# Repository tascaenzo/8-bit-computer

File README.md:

# CPU 8-bit

Repository di supporto alla serie didattica YouTube in cui viene progettata e costruita una CPU a 8 bit partendo dai blocchi logici fondamentali.

In questa fase il repository contiene documentazione, una prima ISA, esempi assembly, un assembler in C e strumenti di supporto per programmare le memorie della CPU.

## Contenuto

```text
.
├── docs/
├── examples/
│   └── assembly/
├── hardware/
│   └── tang-nano-9k-video/
├── tools/
│   ├── assembler/
│   ├── cu-bytecode/
│   └── eeprom-programmer/
├── wiki/
│   ├── blog/
│   └── videos/
└── README.md
```

### `docs`

Contiene la documentazione tecnica della CPU:

- [`docs/isa.md`](docs/isa.md) definisce architettura, istruzioni e opcode;
- [`docs/assembly-language.md`](docs/assembly-language.md) definisce la sintassi dei programmi assembly.
- [`docs/control-unit-microcode.md`](docs/control-unit-microcode.md) definisce segnali e microsequenze della Control Unit.
- [`docs/video-hdmi.md`](docs/video-hdmi.md) definisce VRAM e uscita HDMI della Tang Nano 9K.
- [`docs/io-ps2-timer.md`](docs/io-ps2-timer.md) definisce registri I/O, tastiera PS/2 e timer della Tang Nano 9K.

### `examples/assembly`

Contiene programmi assembly didattici usati per provare l'assembler e spiegare le istruzioni della CPU.

### `hardware/tang-nano-9k-video`

Contiene il progetto FPGA video completo: interfaccia CPU, VRAM 16 KiB,
font ASCII e uscita HDMI 640 × 480. Il [README FPGA](hardware/tang-nano-9k-video/README.md)
include build, test, pinout e caricamento del bitstream. La build e' verificata
con OSS CAD Suite; il collaudo sulla scheda fisica resta da eseguire.

### `tools/assembler`

Contiene `cpu8asm`, l'assembler in C che traduce i programmi assembly in byte macchina.

### `tools/eeprom-programmer`

Contiene sketch e documentazione per programmare EEPROM parallele usate dalla CPU, come la AT28C64.

La guida passo passo per il programmatore AT28C64 con Arduino Mega e in:

```text
docs/at28c64-arduino-mega-programmer.md
```

### `tools/cu-bytecode`

Contiene `cpu8microcode`, il generatore C delle tre Control ROM e della ROM di
dispatch. La guida di build e la mappa dei bit sono in
[`tools/cu-bytecode/README.md`](tools/cu-bytecode/README.md).

### `tools/simulator-web`

Contiene il simulatore web step-by-step della ISA: permette di assemblare ed
eseguire programmi nel browser, osservando registri, flag, RAM e la memoria
video mappata nella FPGA. La guida di avvio è in
[`tools/simulator-web/README.md`](tools/simulator-web/README.md).

### `wiki/videos`

Contiene le trascrizioni autogenerate dei video della serie.

Le trascrizioni sono materiale grezzo: possono contenere errori di riconoscimento, frasi incomplete o termini tecnici interpretati male. Servono come base di lavoro per ricostruire gli argomenti trattati nei video.

### `wiki/blog`

Contiene articoli tecnici in italiano ricavati dalle trascrizioni e dagli argomenti gia affrontati.

Gli articoli seguono il percorso reale della serie e non anticipano parti non ancora consolidate.

## Argomenti documentati

Finora la documentazione copre:

- operazioni logiche della ALU: `AND`, `OR`, `XOR`, `NOR`, `NAND`, `XNOR`, `NOT`;
- pull-up, pull-down e comportamento dei livelli logici;
- buffer tri-state e collegamento al bus dati;
- somma binaria con half adder e full adder;
- complemento a due e numeri con segno;
- somma e sottrazione con il 74283;
- flag `Carry`, `Negative`, `Zero` e `Overflow`;
- operazioni di confronto tramite flag;
- codice operazione della ALU;
- segnale di clock;
- flip-flop `SR` e `D`.

## Convenzioni

- La documentazione principale e in italiano.
- I nomi tecnici possono restare in inglese quando corrispondono meglio a datasheet, segnali o architettura.
- Le trascrizioni autogenerate non sono considerate documentazione definitiva: vanno ripulite e corrette quando vengono trasformate in articoli.

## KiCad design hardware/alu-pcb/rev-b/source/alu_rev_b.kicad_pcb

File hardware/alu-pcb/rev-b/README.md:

# CPU8 — PCB ALU rev. B

Pacchetto per fabbricare una **scheda nuda da saldare**, con sorgenti KiCad.
Versione del 7 ottobre 2026: ALU combinatoria a 8 bit, logica **74HCT a 5 V**,
registri RA/RB e registro dei flag **esterni**. La revisione B aggiunge indicatori e comandi locali alla revisione A.

## File da usare

- `CPU8_ALU_REV_B_GERBER.zip`: caricare questo ZIP nel preventivatore PCB.
- `CPU8_ALU_REV_B_PROJECT.zip`: progetto modificabile e documentazione.
- `source/alu_rev_b.kicad_pro`: aprire in KiCad per accedere a schema e PCB.
- `alu_rev_b_schematic.pdf`: schema completo, con tutti i pin e le reti.
- `BOM.csv`: componenti da acquistare per il montaggio manuale.
- `alu_rev_b_preview.png`: anteprima della scheda nuda.
- `alu_rev_b_layout.svg`: visualizzazione delle piste e della serigrafia.

Lo ZIP Gerber non include i componenti: non è un ordine di assemblaggio.
Non sono stati effettuati ordini o caricamenti sui siti dei produttori.

## Parametri per l'ordine

| Parametro | Impostazione |
| --- | --- |
| Dimensioni | 290 × 300 mm |
| Materiale | FR-4 |
| Strati rame | 2 |
| Spessore | 1,6 mm |
| Rame | 1 oz |
| Maschera | Verde, entrambi i lati |
| Serigrafia | Bianca, fronte |
| Finitura | HASL senza piombo oppure ENIG |
| Assemblaggio | Nessuno; componenti saldati a mano |
| Stencil | Nessuno |
| Via | Diametro rame 0,70 mm, foro 0,30 mm |
| Fori componenti | 0,80 e 0,90 mm, metallizzati |
| Fori montaggio | Quattro fori da 3,20 mm, non metallizzati |

Le piste sono generalmente da 0,30 mm, con restringimenti locali fino a
0,15 mm. Le regole di clearance del progetto sono 0,25 mm; clearance minima
assoluta verificata 0,20 mm. Gli anelli delle via sono da 0,20 mm.
Le capacità pubblicate da [JLCPCB](https://jlcpcb.com/capabilities/Capabilities)
e [PCBWay](https://www.pcbway.com/capabilities.html) consentono queste dimensioni
con rame da 1 oz. Verificare che l'anteprima del produttore riconosca tutti
i layer e i due file di foratura e mostri 290 × 300 mm.

## Cosa contiene la scheda

Dieci operazioni, due sommatori a quattro bit in cascata, selezione del
risultato mediante otto multiplexer, buffer tri-state del bus e flag
combinatori C/Z/N/O. Nessun clock è necessario sulla scheda: i registri che
catturano dati e flag si trovano all'esterno.

La selezione mediante multiplexer modifica l'implementazione fisica descritta
negli articoli con decoder e buffer separati, mantenendo la semantica della ISA.
Non si tratta di una copia delle connessioni della millefori esistente.

| OP3 OP2 OP1 OP0 | Operazione | Risultato |
| --- | --- | --- |
| 0000 | AND | A AND B |
| 0001 | OR | A OR B |
| 0010 | XOR | A XOR B |
| 0011 | NOR | NOT(A OR B) |
| 0100 | NAND | NOT(A AND B) |
| 0101 | XNOR | NOT(A XOR B) |
| 0110 | NOT | NOT A |
| 0111 | ADD | A + B, modulo 256 |
| 1000 | SUB | A - B, modulo 256 |
| 1001 | CMP | Sottrazione interna; bus disabilitato |
| 1010–1111 | Riservate | Bus disabilitato; flag non definiti per la ISA |

C indica carry in ADD e **borrow** in SUB/CMP. Z indica risultato zero;
N è il bit 7 del risultato; O indica overflow signed. C e O sono azzerati
per le operazioni logiche. I flag derivano dal risultato interno, anche quando
il buffer del bus è disabilitato.

## LED e modalità autonoma

- **16 LED verdi** mostrano A7…A0 e B7…B0 dopo la selezione della sorgente.
- **4 LED gialli** mostrano C, Z, N e O del risultato interno.
- **10 LED blu** mostrano AND, OR, XOR, NOR, NAND, XNOR, NOT, ADD, SUB e CMP.
  Gli opcode riservati non accendono alcun LED di operazione.
- **SW4 OFF = esterna**, **SW4 ON = locale**. Sei 74HCT157 commutano tutti
  i 21 segnali: A, B, opcode e ALU_EN_n. Le due sorgenti restano separate;
  gli interruttori non portano +5 V sulle uscite dei moduli esterni.
- **SW1** imposta A, **SW2** B: da sinistra bit 7, 6, 5, 4, 3, 2, 1, 0.
  **SW3** imposta l'opcode: da sinistra OP3, OP2, OP1, OP0.
  Per ciascun contatto, OFF = 0 e ON = 1.
- **SW5 OFF** disabilita il bus in modalità locale; **SW5 ON** lo abilita.
  CMP e gli opcode riservati mantengono comunque J4 in alta impedenza.
  In modalità esterna SW5 non interviene: decide J3 pin 5.

Per il primo test standalone collegare solo J6 a 5 V regolati e GND,
lasciare J4 scollegato, mettere SW4 ON e scegliere A/B/OP mediante SW1–SW3.
Il risultato interno è disponibile su J7; i LED indicano operandi, flag e
operazione. Questa revisione non include otto LED di risultato.
Esempio ADD: SW1 = 11111111, SW2 = 00000001, SW3 = 0111:
si accendono ADD, C e Z; N/O sono spenti; J7 vale 00.

I LED di A/B/flag sono pilotati da tre buffer 74HCT244 dedicati;
i due 74HCT138 decodificano l'operazione. Ogni LED ha una resistenza da
2,2 kΩ, con corrente nell'ordine di 1 mA: usare LED ad alta efficienza.
I flag sono combinatori e non memorizzati: possono cambiare durante lo
spostamento dei DIP switch. Cambiare sorgente con il bus disabilitato
su entrambe le sorgenti e attendere l'assestamento prima della cattura.

## Connettori

Tutti i connettori hanno due colonne, passo 2,54 mm. Guardando il lato componenti,
con il testo della scheda in alto, il pin 1 è la piazzola quadrata in alto a
sinistra. La prima riga contiene 1/2, la seconda 3/4, e così via.
La piedinatura è specifica di questa scheda: preparare i cavi di conseguenza.

| Connettore | Pin | Segnali |
| --- | --- | --- |
| J1 A_INPUT | 1–8; 9–10 | A0…A7; GND, GND |
| J2 B_INPUT | 1–8; 9–10 | B0…B7; GND, GND |
| J3 CONTROL | 1, 2, 3, 4 | OP0, OP1, OP2, OP3 |
| J3 CONTROL | 5; 6–8 | ALU_EN_n; GND, GND, GND |
| J4 DATA_BUS | 1–8; 9–10 | D0…D7; GND, GND |
| J5 FLAGS_CZNO | 1–6 | C, Z, N, O, GND, GND |
| J6 POWER_5V | 1–4 | +5V, GND, +5V, GND |
| J7 RESULT_TEST | 1–8; 9–10 | R0…R7 interni; GND, GND |

ALU_EN_n = 1 disabilita l'uscita sul bus. ALU_EN_n = 0 la abilita solo
per OP 0…8; CMP e gli opcode riservati lasciano comunque D in alta impedenza.
Un pull-up da 4,7 kΩ disabilita l'uscita quando il controllo è scollegato.
A/B/opcode hanno pull-down da 10 kΩ.

J5 e J7 sono uscite push-pull: usarle come ingressi di altri circuiti o punti
di misura, senza collegarle a un bus pilotato da altre sorgenti. J4 è l'unica
uscita dati tri-state. Collegare le masse dei moduli.

Gli ingressi HCT accettano livelli TTL, ma alimentare questa scheda con 5 V
regolati; non collegare le sue uscite da 5 V direttamente a una FPGA a 3,3 V.
La compatibilità e il carico dei moduli esterni vanno verificati con le sigle
complete degli integrati effettivamente utilizzati.

## Componenti e montaggio

La distinta contiene 172 componenti: 45 IC, 45 condensatori da 100 nF, un
condensatore da 10 µF, sei reti resistive, 33 resistori, sette connettori,
30 LED e cinque DIP switch. Aggiungere **23 zoccoli DIP-14, 18 DIP-16 e quattro DIP-20**, tutti larghi 7,62 mm.
Non sostituire i package DIP con SOIC. Per i multiplexer utilizzare CD74HCT151E:
la distinzione fra uscita diretta Y (pin 5) e complementare W (pin 6) segue
il datasheet TI attuale.

- Orientare la tacca degli IC verso l'alto; il pin 1 ha piazzola quadrata.
- RN1…RN6 devono essere **reti bussed SIP-9**, comune al pin 1:
  otto resistenze da 10 kΩ verso il comune. Le reti a resistenze isolate
  non sono compatibili.
- C46 è il condensatore elettrolitico da 10 µF: **pin 1 positivo**, pin 2 GND.
- C1…C45 sono ceramici non polarizzati, passo 2,50 mm e corpo entro 4 × 3 mm.
- SW1/SW2: C&K **SDA08H0BD**; SW3: **SDA04H0BD**;
  SW4/SW5: **SDA01H0BD**, versioni through-hole. Passo contatti 2,54 mm,
  distanza fra le file 7,62 mm, contatti SPST opposti. Orientare il corpo
  come indicato in serigrafia e verificare ON prima di saldare.
- LED da 3 mm, passo 2,54 mm: **pin 1 K/catodo**, **pin 2 A/anodo**.
  Il catodo è indicato dalla linea piatta in serigrafia. Nelle spie di
  operazione il catodo è collegato al decoder, non direttamente a GND.
- R1/R3 sono 4,7 kΩ, R2 è 10 kΩ, R4…R33 sono 2,2 kΩ;
  resistori assiali 1/4 W, passo 7,62 mm.
- U34…U39: **SN74HCT157N**; U44/U45: **SN74HCT138N**;
  U33/U40/U41/U42: **SN74HCT244N**, package PDIP.
- Le connessioni al piano di massa sono solide. Saldare i pin GND con
  una punta adeguata e sufficiente trasferimento di calore.

## Verifiche effettuate e collaudo

- Simulazione statica a livello di pin degli IC su **4.194.304 combinazioni**
  A/B/OP/enable in entrambe le modalità, con sorgente inattiva complementata, comprese le operazioni valide, flag e stato del buffer.
- ERC dello schema: **0 violazioni**.
- DRC del PCB: **0 violazioni**, **0 collegamenti mancanti**.
- Corrispondenza PCB/schema: **0 problemi**.
- Esportazione Gerber e foratura tramite KiCad 10.0.7.

I rapporti sono nella cartella `verification`. Questi controlli verificano
il progetto digitale e il layout; **nessun prototipo fisico è stato montato
né collaudato**. La frequenza massima, i carichi dei cavi e i tempi di
assestamento non sono stati misurati: iniziare con operandi e opcode statici,
poi con clock manuale e misurare prima di aumentare la frequenza.

Prima di inserire gli IC, controllare il montaggio e l'alimentazione degli
zoccoli. Eseguire i primi test con un alimentatore da banco a corrente limitata.
Disabilitare l'uscita durante il cambio di opcode e attendere l'assestamento
prima che i registri esterni catturino risultato e flag. Nessun altro modulo
può pilotare J4 mentre questa ALU è abilitata.

| Operazione | A | B | R interno | C | Z | N | O |
| --- | --- | --- | --- | --- | --- | --- | --- |
| AND | A5 | 3C | 24 | 0 | 0 | 0 | 0 |
| ADD | FF | 01 | 00 | 1 | 1 | 0 | 0 |
| ADD | 7F | 01 | 80 | 0 | 0 | 1 | 1 |
| SUB | 05 | 0A | FB | 1 | 0 | 1 | 0 |
| SUB | 80 | 01 | 7F | 0 | 0 | 0 | 1 |
| CMP | 03 | 03 | 00 | 0 | 1 | 0 | 0 |

I numeri nella tabella sono esadecimali. Per CMP leggere R su J7 e verificare
che J4 resti ad alta impedenza. Per questo test usare un carico resistivo
appropriato o una sonda: il valore letto su un bus flottante non prova lo
stato tri-state.

## Riferimenti

Semantica: `docs/isa.md` e `docs/control-unit-microcode.md` del repository.
Piedinature controllate sui datasheet ufficiali:
[CD74HCT151](https://www.ti.com/lit/ds/symlink/cd74hct151.pdf),
[CD74HCT283](https://www.ti.com/lit/ds/symlink/cd74hct283.pdf),
[SN74HCT244](https://www.ti.com/lit/ds/symlink/sn74hct244.pdf),
[SN74HCT02](https://www.ti.com/lit/ds/symlink/sn74hct02.pdf),
[SN74HCT157](https://www.ti.com/lit/ds/symlink/sn74hct157.pdf),
[SN74HCT138](https://www.ti.com/lit/ds/symlink/sn74hct138.pdf),
[C&K SDA](https://www.ckswitches.com/media/1327/sda.pdf).

Gli script in `tools` documentano la generazione iniziale e le verifiche.
`build_alu.py --rebuild-unrouted` ricrea una scheda **senza piste**:
richiede nuovo instradamento, DRC, esportazione e confezionamento. Per normali
modifiche lavorare sui sorgenti KiCad finali, preservando le piste esistenti.

Per ricostruire completamente: generare il layout non instradato; esportare
`source/schematic.xml` con `kicad-cli sch export netlist --format kicadxml`;
eseguire `prepare_board.py` con il Python pcbnew di KiCad; instradare il DSN
esportato e salvare la sessione SES; eseguire `finish_board.py`; verificare
ERC, DRC con parità e simulazione; esportare nuovamente Gerber/forature prima
di usare `package_fabrication.py`. `prepare_board.py` ed `finish_board.py`
richiedono pcbnew; gli altri script usano Python standard.

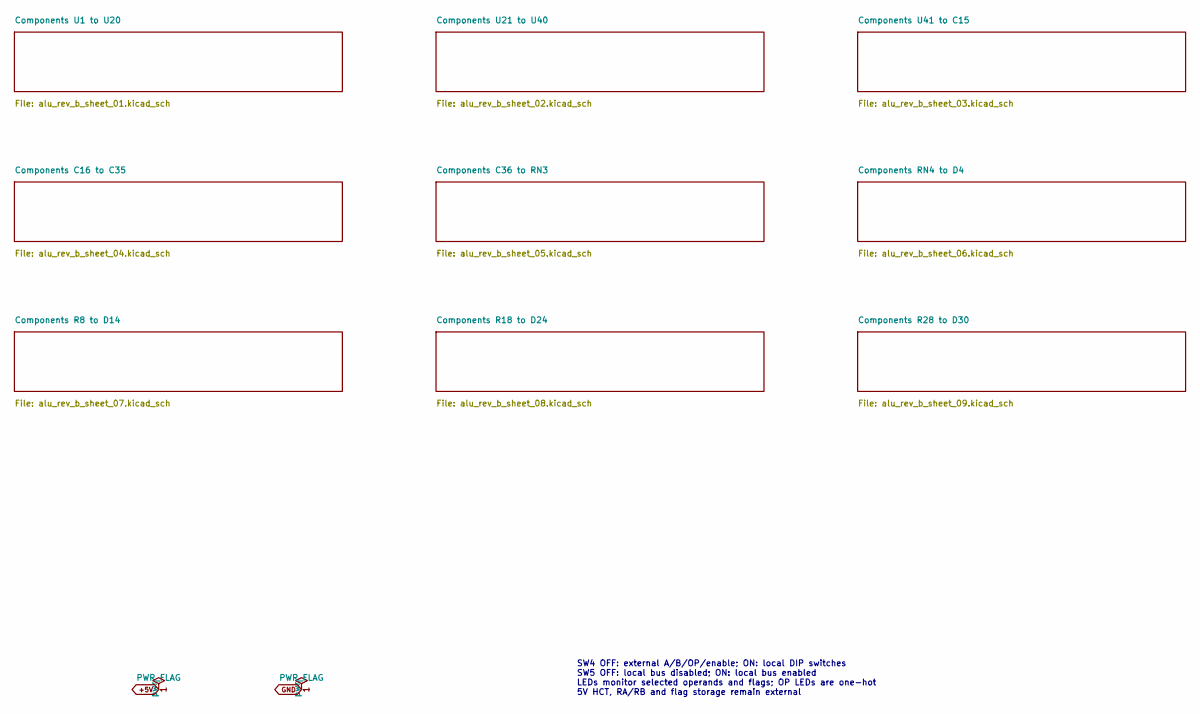
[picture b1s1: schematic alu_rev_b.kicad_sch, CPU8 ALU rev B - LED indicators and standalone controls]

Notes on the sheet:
SW4 OFF: external A/B/OP/enable; ON: local DIP switches SW5 OFF: local bus disabled; ON: local bus enabled LEDs monitor selected operands and flags; OP LEDs are one-hot 5V HCT, RA/RB and flag storage remain external

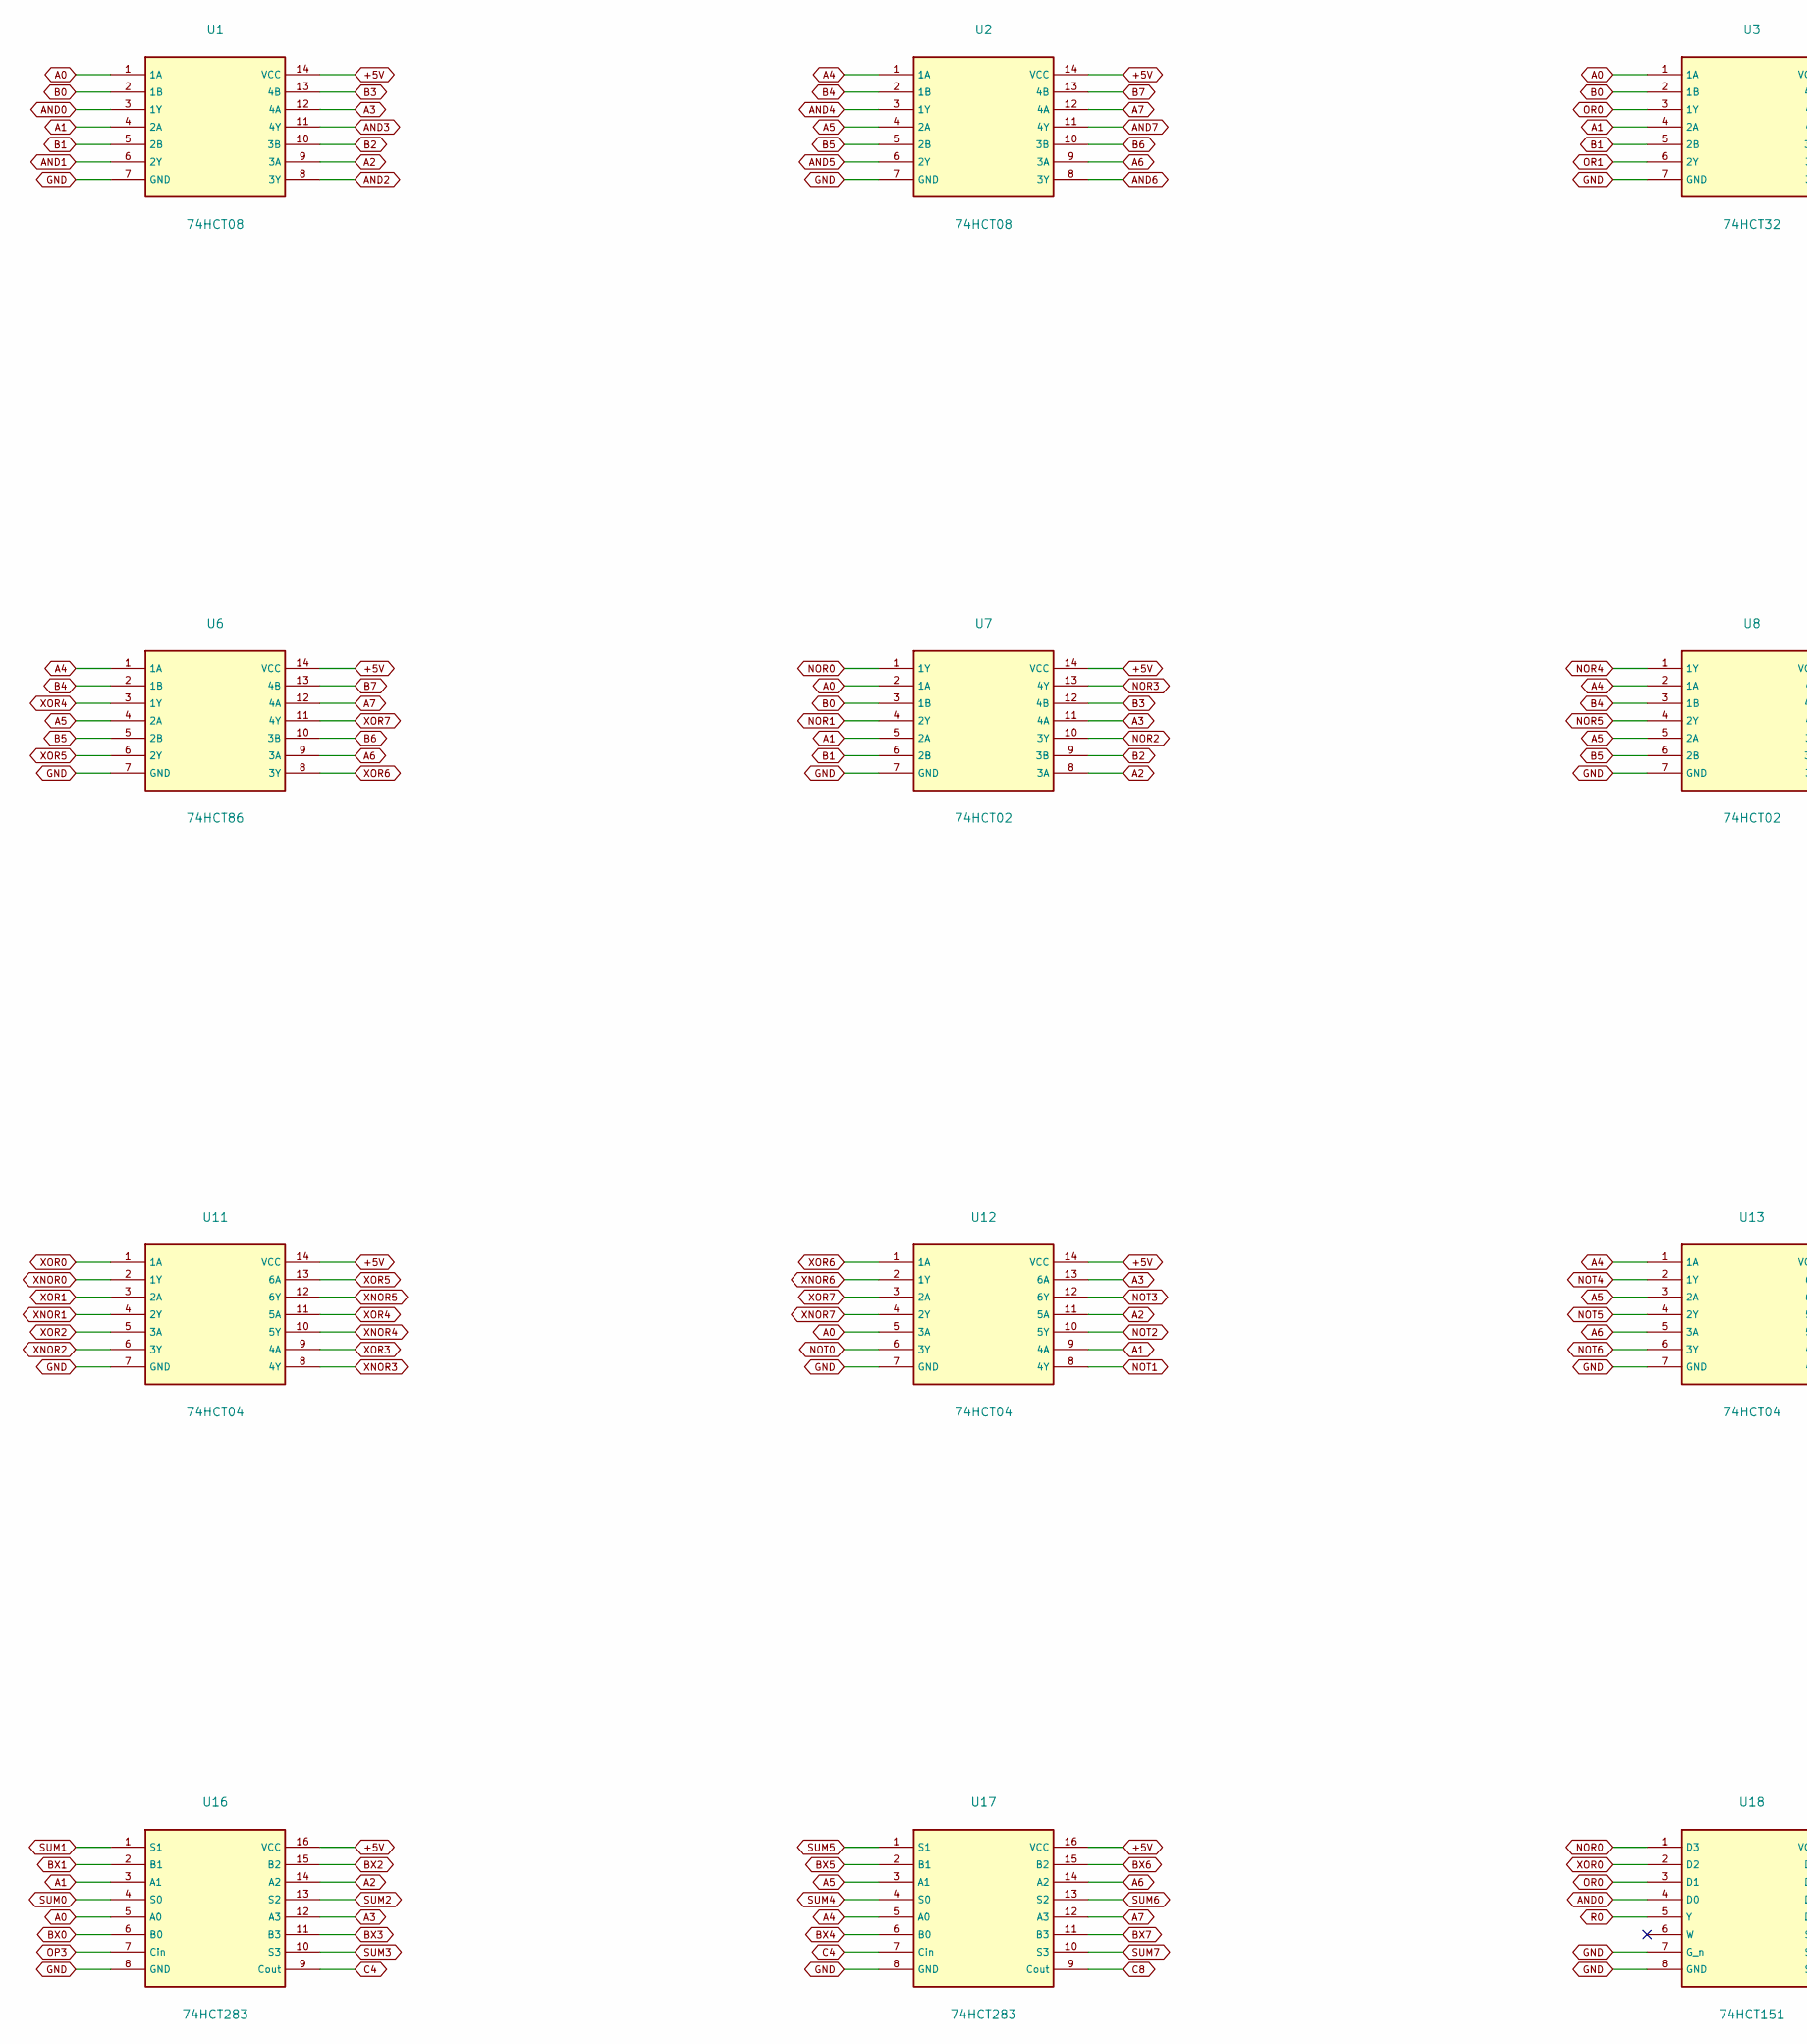
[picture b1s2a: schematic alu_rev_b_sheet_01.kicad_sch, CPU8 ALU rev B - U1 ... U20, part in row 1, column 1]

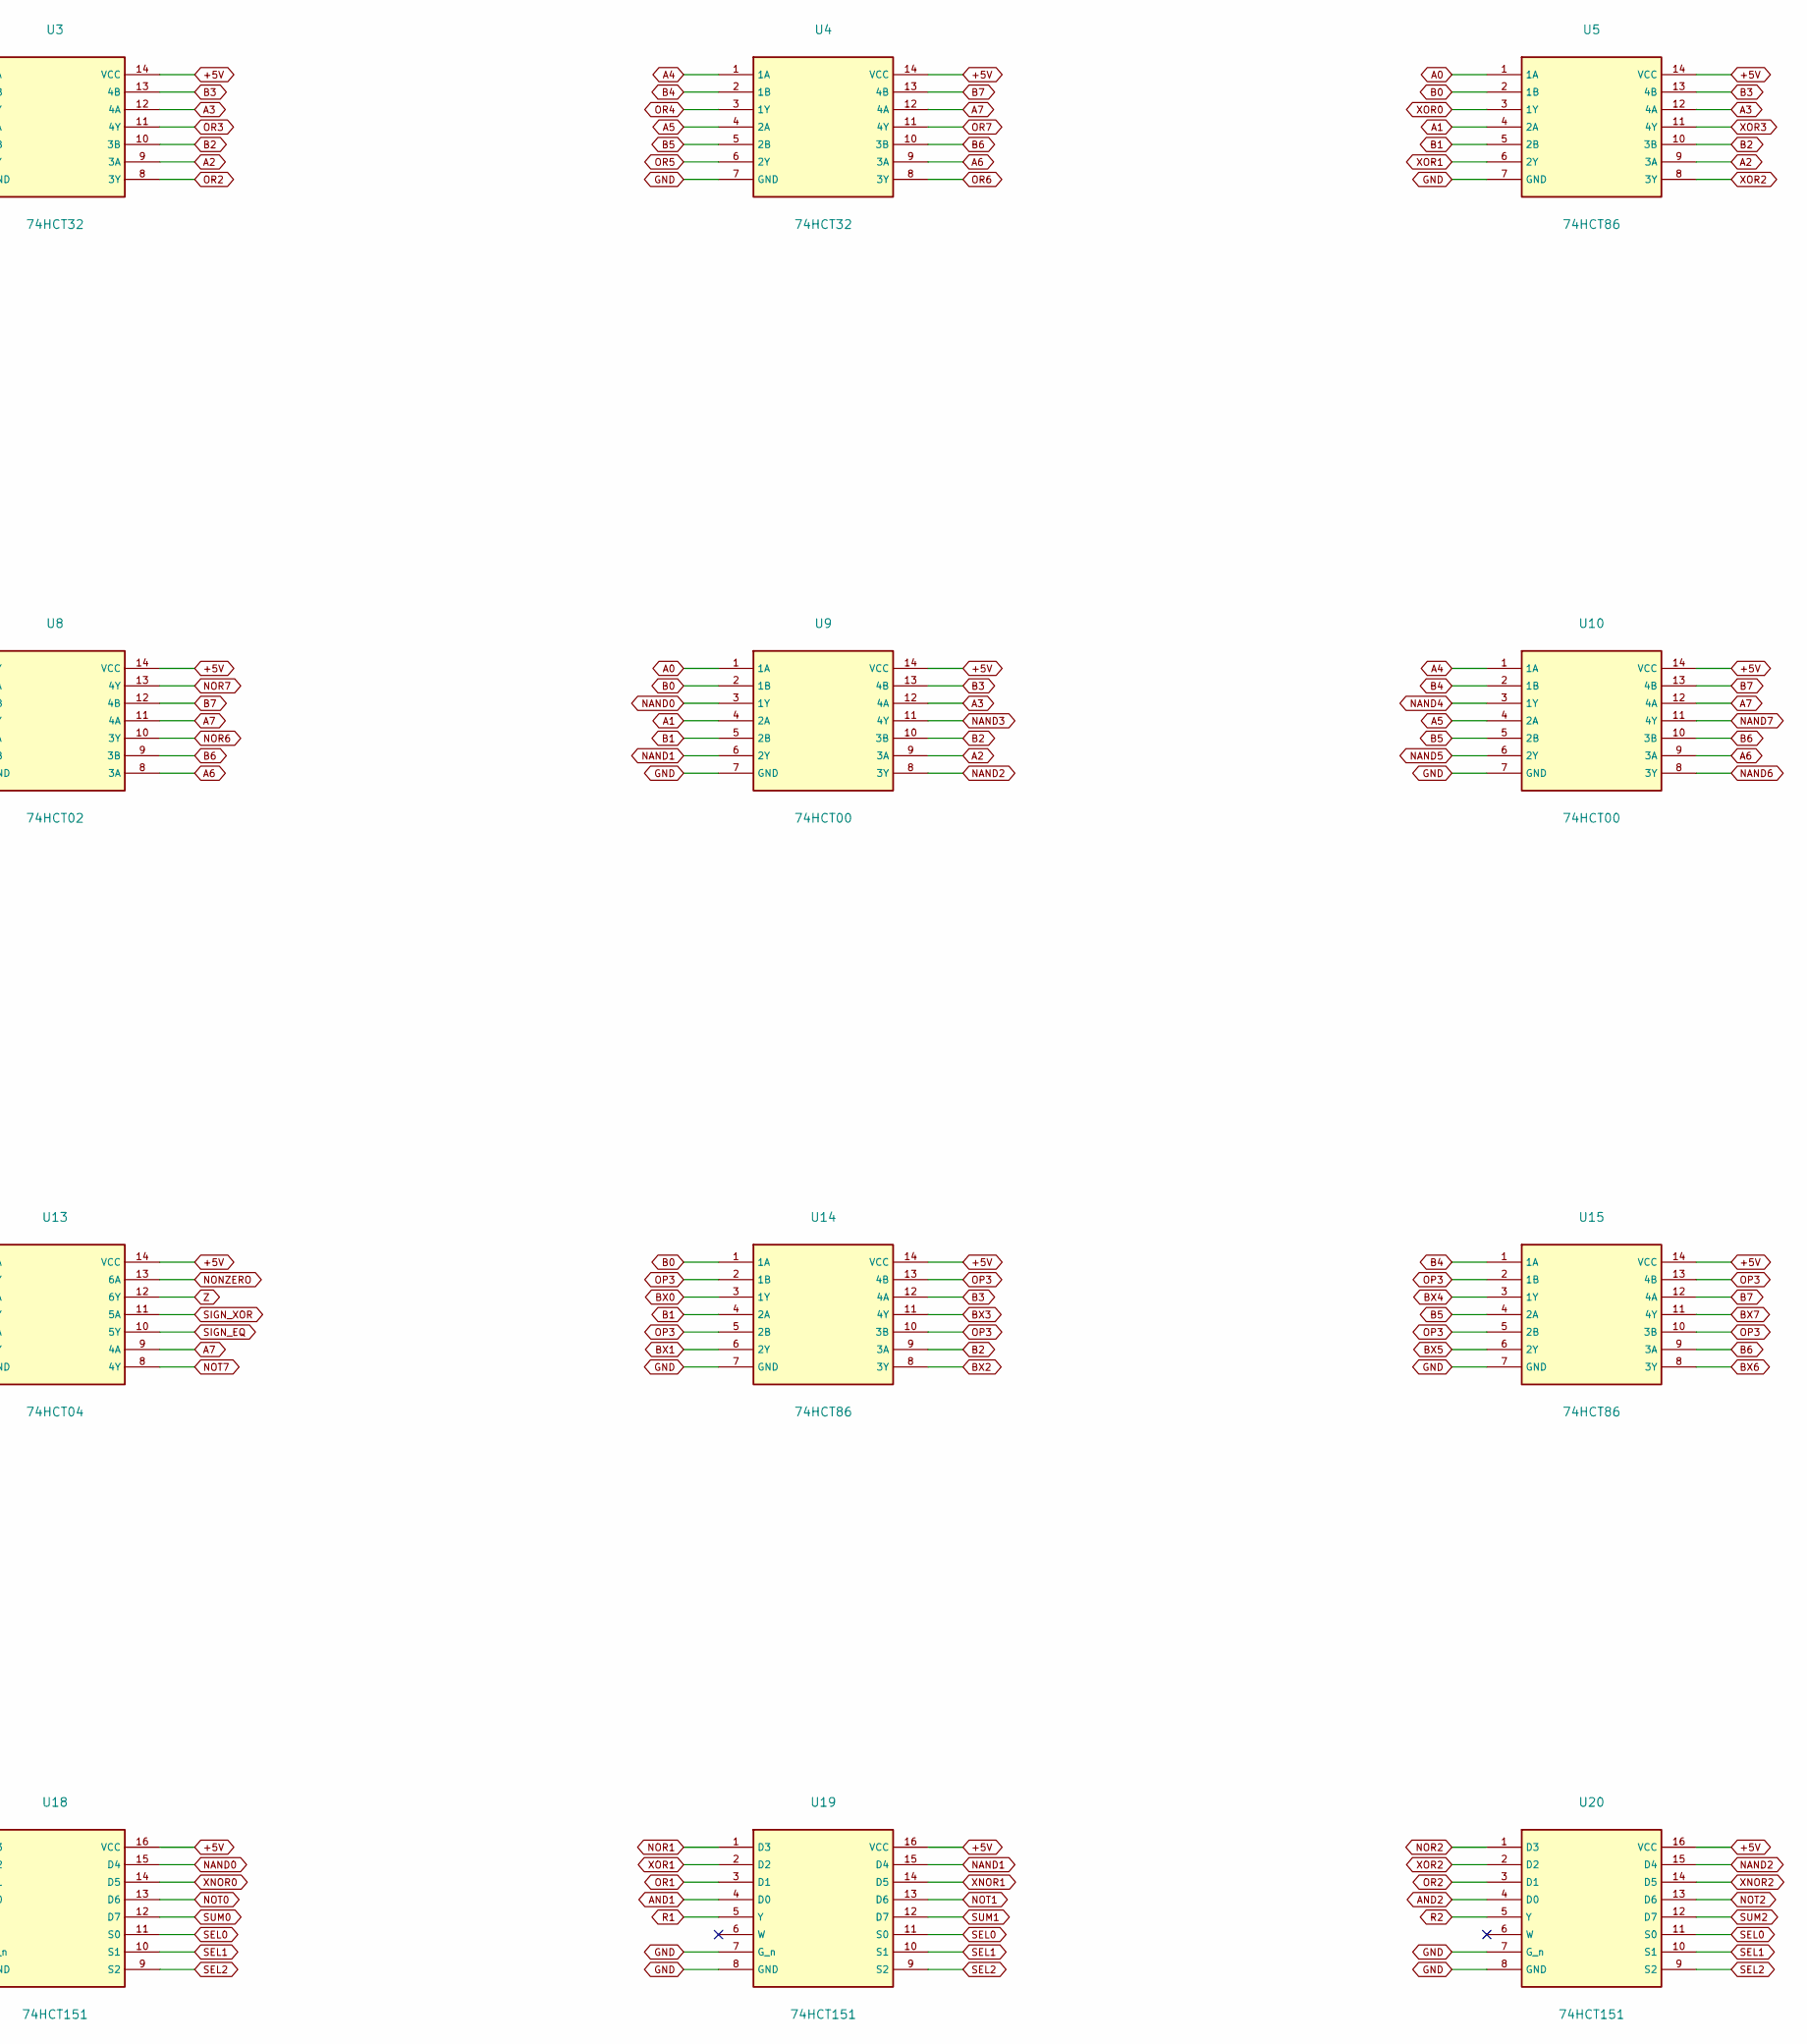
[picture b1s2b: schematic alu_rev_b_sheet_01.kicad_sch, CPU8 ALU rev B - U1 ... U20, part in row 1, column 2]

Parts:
U1, U2: 74HCT08; DIP-14_W7.62mm
U3, U4: 74HCT32; DIP-14_W7.62mm
U5, U6, U14, U15: 74HCT86; DIP-14_W7.62mm
U7, U8: 74HCT02; DIP-14_W7.62mm
U9, U10: 74HCT00; DIP-14_W7.62mm
U11, U12, U13: 74HCT04; DIP-14_W7.62mm
U16, U17: 74HCT283; DIP-16_W7.62mm
U18, U19, U20: 74HCT151; DIP-16_W7.62mm

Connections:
+5V: U1.14 (VCC), U2.14 (VCC), U3.14 (VCC), U4.14 (VCC), U5.14 (VCC), U6.14 (VCC), U7.14 (VCC), U8.14 (VCC), U9.14 (VCC), U10.14 (VCC), U11.14 (VCC), U12.14 (VCC), U13.14 (VCC), U14.14 (VCC), U15.14 (VCC), U16.16 (VCC), U17.16 (VCC), U18.16 (VCC), U19.16 (VCC), U20.16 (VCC); also elsewhere on the board
A0: U1.1 (1A), U3.1 (1A), U5.1 (1A), U7.2 (1A), U9.1 (1A), U12.5 (3A), U16.5 (A0); also elsewhere on the board
A1: U1.4 (2A), U3.4 (2A), U5.4 (2A), U7.5 (2A), U9.4 (2A), U12.9 (4A), U16.3 (A1); also elsewhere on the board
A2: U1.9 (3A), U3.9 (3A), U5.9 (3A), U7.8 (3A), U9.9 (3A), U12.11 (5A), U16.14 (A2); also elsewhere on the board
A3: U1.12 (4A), U3.12 (4A), U5.12 (4A), U7.11 (4A), U9.12 (4A), U12.13 (6A), U16.12 (A3); also elsewhere on the board
A4: U2.1 (1A), U4.1 (1A), U6.1 (1A), U8.2 (1A), U10.1 (1A), U13.1 (1A), U17.5 (A0); also elsewhere on the board
A5: U2.4 (2A), U4.4 (2A), U6.4 (2A), U8.5 (2A), U10.4 (2A), U13.3 (2A), U17.3 (A1); also elsewhere on the board
A6: U2.9 (3A), U4.9 (3A), U6.9 (3A), U8.8 (3A), U10.9 (3A), U13.5 (3A), U17.14 (A2); also elsewhere on the board
A7: U2.12 (4A), U4.12 (4A), U6.12 (4A), U8.11 (4A), U10.12 (4A), U13.9 (4A), U17.12 (A3); also elsewhere on the board
AND0: U1.3 (1Y), U18.4 (D0)
AND1: U1.6 (2Y), U19.4 (D0)
AND2: U1.8 (3Y), U20.4 (D0)
AND3: U1.11 (4Y); also elsewhere on the board
AND4: U2.3 (1Y); also elsewhere on the board
AND5: U2.6 (2Y); also elsewhere on the board
AND6: U2.8 (3Y); also elsewhere on the board
AND7: U2.11 (4Y); also elsewhere on the board
B0: U1.2 (1B), U3.2 (1B), U5.2 (1B), U7.3 (1B), U9.2 (1B), U14.1 (1A); also elsewhere on the board
B1: U1.5 (2B), U3.5 (2B), U5.5 (2B), U7.6 (2B), U9.5 (2B), U14.4 (2A); also elsewhere on the board
B2: U1.10 (3B), U3.10 (3B), U5.10 (3B), U7.9 (3B), U9.10 (3B), U14.9 (3A); also elsewhere on the board
B3: U1.13 (4B), U3.13 (4B), U5.13 (4B), U7.12 (4B), U9.13 (4B), U14.12 (4A); also elsewhere on the board
B4: U2.2 (1B), U4.2 (1B), U6.2 (1B), U8.3 (1B), U10.2 (1B), U15.1 (1A); also elsewhere on the board
B5: U2.5 (2B), U4.5 (2B), U6.5 (2B), U8.6 (2B), U10.5 (2B), U15.4 (2A); also elsewhere on the board
B6: U2.10 (3B), U4.10 (3B), U6.10 (3B), U8.9 (3B), U10.10 (3B), U15.9 (3A); also elsewhere on the board
B7: U2.13 (4B), U4.13 (4B), U6.13 (4B), U8.12 (4B), U10.13 (4B), U15.12 (4A); also elsewhere on the board
BX0: U14.3 (1Y), U16.6 (B0)
BX1: U14.6 (2Y), U16.2 (B1)
BX2: U14.8 (3Y), U16.15 (B2)
BX3: U14.11 (4Y), U16.11 (B3)
BX4: U15.3 (1Y), U17.6 (B0)
BX5: U15.6 (2Y), U17.2 (B1)
BX6: U15.8 (3Y), U17.15 (B2)
BX7: U15.11 (4Y), U17.11 (B3); also elsewhere on the board
C4: U16.9 (Cout), U17.7 (Cin)
C8: U17.9 (Cout); also elsewhere on the board
GND: U1.7 (GND), U2.7 (GND), U3.7 (GND), U4.7 (GND), U5.7 (GND), U6.7 (GND), U7.7 (GND), U8.7 (GND), U9.7 (GND), U10.7 (GND), U11.7 (GND), U12.7 (GND), U13.7 (GND), U14.7 (GND), U15.7 (GND), U16.8 (GND), U17.8 (GND), U18.7 (G_n), U18.8 (GND), U19.7 (G_n), U19.8 (GND), U20.7 (G_n), U20.8 (GND); also elsewhere on the board
NAND0: U9.3 (1Y), U18.15 (D4)
NAND1: U9.6 (2Y), U19.15 (D4)
NAND2: U9.8 (3Y), U20.15 (D4)
NAND3: U9.11 (4Y); also elsewhere on the board
NAND4: U10.3 (1Y); also elsewhere on the board
NAND5: U10.6 (2Y); also elsewhere on the board
NAND6: U10.8 (3Y); also elsewhere on the board
NAND7: U10.11 (4Y); also elsewhere on the board
NONZERO: U13.13 (6A); also elsewhere on the board
NOR0: U7.1 (1Y), U18.1 (D3)
NOR1: U7.4 (2Y), U19.1 (D3)
NOR2: U7.10 (3Y), U20.1 (D3)
NOR3: U7.13 (4Y); also elsewhere on the board
NOR4: U8.1 (1Y); also elsewhere on the board
NOR5: U8.4 (2Y); also elsewhere on the board
NOR6: U8.10 (3Y); also elsewhere on the board
NOR7: U8.13 (4Y); also elsewhere on the board
NOT0: U12.6 (3Y), U18.13 (D6)
NOT1: U12.8 (4Y), U19.13 (D6)
NOT2: U12.10 (5Y), U20.13 (D6)
NOT3: U12.12 (6Y); also elsewhere on the board
NOT4: U13.2 (1Y); also elsewhere on the board
NOT5: U13.4 (2Y); also elsewhere on the board
NOT6: U13.6 (3Y); also elsewhere on the board
NOT7: U13.8 (4Y); also elsewhere on the board
OP3: U14.2 (1B), U14.5 (2B), U14.10 (3B), U14.13 (4B), U15.2 (1B), U15.5 (2B), U15.10 (3B), U15.13 (4B), U16.7 (Cin); also elsewhere on the board
OR0: U3.3 (1Y), U18.3 (D1)
OR1: U3.6 (2Y), U19.3 (D1)
OR2: U3.8 (3Y), U20.3 (D1)
OR3: U3.11 (4Y); also elsewhere on the board
OR4: U4.3 (1Y); also elsewhere on the board
OR5: U4.6 (2Y); also elsewhere on the board
OR6: U4.8 (3Y); also elsewhere on the board
OR7: U4.11 (4Y); also elsewhere on the board
R0: U18.5 (Y); also elsewhere on the board
R1: U19.5 (Y); also elsewhere on the board
R2: U20.5 (Y); also elsewhere on the board
SEL0: U18.11 (S0), U19.11 (S0), U20.11 (S0); also elsewhere on the board
SEL1: U18.10 (S1), U19.10 (S1), U20.10 (S1); also elsewhere on the board
SEL2: U18.9 (S2), U19.9 (S2), U20.9 (S2); also elsewhere on the board
SIGN_EQ: U13.10 (5Y); also elsewhere on the board
SIGN_XOR: U13.11 (5A); also elsewhere on the board
SUM0: U16.4 (S0), U18.12 (D7)
SUM1: U16.1 (S1), U19.12 (D7)
SUM2: U16.13 (S2), U20.12 (D7)
SUM3: U16.10 (S3); also elsewhere on the board
SUM4: U17.4 (S0); also elsewhere on the board
SUM5: U17.1 (S1); also elsewhere on the board
SUM6: U17.13 (S2); also elsewhere on the board
SUM7: U17.10 (S3); also elsewhere on the board
XNOR0: U11.2 (1Y), U18.14 (D5)
XNOR1: U11.4 (2Y), U19.14 (D5)
XNOR2: U11.6 (3Y), U20.14 (D5)
XNOR3: U11.8 (4Y); also elsewhere on the board
XNOR4: U11.10 (5Y); also elsewhere on the board
XNOR5: U11.12 (6Y); also elsewhere on the board
XNOR6: U12.2 (1Y); also elsewhere on the board
XNOR7: U12.4 (2Y); also elsewhere on the board
XOR0: U5.3 (1Y), U11.1 (1A), U18.2 (D2)
XOR1: U5.6 (2Y), U11.3 (2A), U19.2 (D2)
XOR2: U5.8 (3Y), U11.5 (3A), U20.2 (D2)
XOR3: U5.11 (4Y), U11.9 (4A); also elsewhere on the board
XOR4: U6.3 (1Y), U11.11 (5A); also elsewhere on the board
XOR5: U6.6 (2Y), U11.13 (6A); also elsewhere on the board
XOR6: U6.8 (3Y), U12.1 (1A); also elsewhere on the board
XOR7: U6.11 (4Y), U12.3 (2A); also elsewhere on the board
Z: U13.12 (6Y); also elsewhere on the board
